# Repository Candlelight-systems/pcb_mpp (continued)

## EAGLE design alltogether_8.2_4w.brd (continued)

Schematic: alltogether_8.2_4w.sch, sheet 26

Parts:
C434: 120n; 0402-CAP
C435, C436, C446, C447: 0.1u; 0402-CAP
C437, C438, C439, C440, C443: 0.1u; 0402
C441, C442: 1n; 0402
C444: 0.1u; 0603-CAP
C445: 22u; 0805
C448: 1n; 0402-CAP
D216, D217, D218, D219, D220, D221, D222: BAT20JFILM; SOD-323
D223, D224: TVSSMA; SMA-DIODE
IC65: OPA237U; SO08
IC66, IC67: INA118U; SO08
JP63, JP64, JP65: JUMPER-PAD-3-NC_BY_PASTE; PAD-JUMPER-3-NC_BY_PASTE_YES_SILK_FULL_BOX
K27: DSBT2-M-2D-DC1.5V; DS-BT
LED21: GREEN; CHIPLED_0603
Q38: MOSFET-NCHANNELAO3404A; SOT23-3
R512, R518, R522, R526, R528: 10k; 0402-RES
R513: 0.001; 2512
R514: 0; 0402-RES
R515: 125; 1206
R516, R519, R530, R531: 250; 0402-RES
R517, R529: 100k; 0402-RES
R520, R521: 47; 0402-RES
R523: 0; 1206
R524, R525: 125; 0402-RES
R527: 0; 0805
TP87, TP88, TP89, TP90: TESTPOINT0.1"; 1X01_ROUND
U$95, U$96, U$97: SPTAF1/2-3.5
U$98: MUX509; R-PDSO-G16

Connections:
A0: TP90.1, U$98.P$1 (A0); also elsewhere on the board
DAC11: R516.1, R529.2, TP89.1; also elsewhere on the board
FB11: JP65.3, R528.1
GND: C434.2, C435.2, C436.2, C437.2, C438.2, C439.1, C440.1, C441.1, C442.2, C446.1, C447.1, D223.C, D224.C, IC66.5 (REF), IC67.5 (REF), Q38.2 (S), R517.1, R522.1, R529.1, U$96.P$1, U$96.P$2, U$98.P$6 (S3A), U$98.P$11 (S3B), U$98.P$15 (GND); also elsewhere on the board
unnamed: D216.A, D217.C, K27.4, R513.2, R526.1, R531.1
unnamed: K27.13, R519.2
unnamed: IC66.1 (RG), R515.1
unnamed: IC66.8 (RG), R515.2
unnamed: C434.1, IC65.3 (+IN), R516.2
unnamed: D218.A, K27.16 (-), Q38.3 (D), R518.1
unnamed: LED21.C, R518.2
unnamed: C443.1, C444.1, IC65.2 (-IN), JP65.2, R522.2
unnamed: C443.2, C445.2, R512.2, R513.1, R527.2, R530.1, U$95.P$3, U$95.P$4
unnamed: IC66.6 (OUT), R520.1
unnamed: IC67.6 (OUT), JP63.3, R521.1, R528.2
unnamed: C444.2, C445.1, IC65.6 (OUT), R514.1, R527.1
unnamed: IC67.1 (RG), R523.1
unnamed: IC67.8 (RG), R523.2
unnamed: IC67.2 (-IN), JP63.2
unnamed: IC67.3 (+IN), JP64.2
unnamed: D221.C, D222.A, D224.A, JP63.1, R524.2
unnamed: R524.1, U$97.P$3, U$97.P$4
unnamed: D219.C, D220.A, D223.A, JP64.1, R525.2
unnamed: R525.1, U$97.P$1, U$97.P$2
unnamed: JP64.3, R526.2
unnamed: JP65.1, R512.1, R519.1
unnamed: R514.2, U$95.P$1, U$95.P$2
unnamed: IC66.2 (-IN), U$98.P$8 (DA)
unnamed: IC66.3 (+IN), U$98.P$9 (DB)
unnamed: C448.2, R531.2, U$98.P$10 (S4B)
unnamed: C448.1, R530.2, U$98.P$7 (S4A)
OUT11: K27.8 (S), K27.9 (S), U$96.P$3, U$96.P$4
SENSEI11: C442.1, R520.2, TP87.1; also elsewhere on the board
SENSEV11: C441.2, R521.2, TP88.1; also elsewhere on the board
SWITCH11: Q38.1 (G), R517.2; also elsewhere on the board
VCC: C436.1, C438.1, C440.2, C446.2, D216.C, D218.C, D220.C, D222.C, IC65.7 (V+), IC66.7 (V+), IC67.7 (V+), K27.1 (+), LED21.A, U$98.P$2 (EN), U$98.P$14 (V+), U$98.P$16 (A1); also elsewhere on the board
VDD: C435.1, C437.1, C439.2, C447.2, D217.A, D219.A, D221.A, IC65.4 (V-), IC66.4 (V-), IC67.4 (V-), U$98.P$3 (V-); also elsewhere on the board

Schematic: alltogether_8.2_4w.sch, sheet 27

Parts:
C464: 120n; 0402-CAP
C465, C466, C476, C477: 0.1u; 0402-CAP
C467, C468, C469, C470, C473: 0.1u; 0402
C471, C472: 1n; 0402
C474: 0.1u; 0603-CAP
C475: 22u; 0805
C478: 1n; 0402-CAP
D234, D235, D236, D237, D238, D239, D240: BAT20JFILM; SOD-323
D241, D242: TVSSMA; SMA-DIODE
IC71: OPA237U; SO08
IC72, IC73: INA118U; SO08
JP69, JP70, JP71: JUMPER-PAD-3-NC_BY_PASTE; PAD-JUMPER-3-NC_BY_PASTE_YES_SILK_FULL_BOX
K29: DSBT2-M-2D-DC1.5V; DS-BT
LED23: GREEN; CHIPLED_0603
Q40: MOSFET-NCHANNELAO3404A; SOT23-3
R552, R558, R562, R566, R568: 10k; 0402-RES
R553: 0.001; 2512
R554: 0; 0402-RES
R555: 125; 1206
R556, R559, R570, R571: 250; 0402-RES
R557, R569: 100k; 0402-RES
R560, R561: 47; 0402-RES
R563: 0; 1206
R564, R565: 125; 0402-RES
R567: 0; 0805
TP95, TP96, TP97, TP98: TESTPOINT0.1"; 1X01_ROUND
U$103, U$104, U$105: SPTAF1/2-3.5
U$106: MUX509; R-PDSO-G16

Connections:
A0: TP98.1, U$106.P$1 (A0); also elsewhere on the board
DAC12: R556.1, R569.2, TP97.1; also elsewhere on the board
FB12: JP71.3, R568.1
GND: C464.2, C465.2, C466.2, C467.2, C468.2, C469.1, C470.1, C471.1, C472.2, C476.1, C477.1, D241.C, D242.C, IC72.5 (REF), IC73.5 (REF), Q40.2 (S), R557.1, R562.1, R569.1, U$104.P$1, U$104.P$2, U$106.P$6 (S3A), U$106.P$11 (S3B), U$106.P$15 (GND); also elsewhere on the board
unnamed: D234.A, D235.C, K29.4, R553.2, R566.1, R571.1
unnamed: K29.13, R559.2
unnamed: IC72.1 (RG), R555.1
unnamed: IC72.8 (RG), R555.2
unnamed: C464.1, IC71.3 (+IN), R556.2
unnamed: D236.A, K29.16 (-), Q40.3 (D), R558.1
unnamed: LED23.C, R558.2
unnamed: C473.1, C474.1, IC71.2 (-IN), JP71.2, R562.2
unnamed: C473.2, C475.2, R552.2, R553.1, R567.2, R570.1, U$103.P$3, U$103.P$4
unnamed: IC72.6 (OUT), R560.1
unnamed: IC73.6 (OUT), JP69.3, R561.1, R568.2
unnamed: C474.2, C475.1, IC71.6 (OUT), R554.1, R567.1
unnamed: IC73.1 (RG), R563.1
unnamed: IC73.8 (RG), R563.2
unnamed: IC73.2 (-IN), JP69.2
unnamed: IC73.3 (+IN), JP70.2
unnamed: D239.C, D240.A, D242.A, JP69.1, R564.2
unnamed: R564.1, U$105.P$3, U$105.P$4
unnamed: D237.C, D238.A, D241.A, JP70.1, R565.2
unnamed: R565.1, U$105.P$1, U$105.P$2
unnamed: JP70.3, R566.2
unnamed: JP71.1, R552.1, R559.1
unnamed: R554.2, U$103.P$1, U$103.P$2
unnamed: IC72.2 (-IN), U$106.P$8 (DA)
unnamed: IC72.3 (+IN), U$106.P$9 (DB)
unnamed: C478.2, R571.2, U$106.P$10 (S4B)
unnamed: C478.1, R570.2, U$106.P$7 (S4A)
OUT12: K29.8 (S), K29.9 (S), U$104.P$3, U$104.P$4
SENSEI12: C472.1, R560.2, TP95.1; also elsewhere on the board
SENSEV12: C471.2, R561.2, TP96.1; also elsewhere on the board
SWITCH12: Q40.1 (G), R557.2; also elsewhere on the board
VCC: C466.1, C468.1, C470.2, C476.2, D234.C, D236.C, D238.C, D240.C, IC71.7 (V+), IC72.7 (V+), IC73.7 (V+), K29.1 (+), LED23.A, U$106.P$2 (EN), U$106.P$14 (V+), U$106.P$16 (A1); also elsewhere on the board
VDD: C465.1, C467.1, C469.2, C477.2, D235.A, D237.A, D239.A, IC71.4 (V-), IC72.4 (V-), IC73.4 (V-), U$106.P$3 (V-); also elsewhere on the board

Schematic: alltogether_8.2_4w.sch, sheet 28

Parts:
C494: 120n; 0402-CAP
C495, C496, C506, C507: 0.1u; 0402-CAP
C497, C498, C499, C500, C503: 0.1u; 0402
C501, C502: 1n; 0402
C504: 0.1u; 0603-CAP
C505: 22u; 0805
C508: 1n; 0402-CAP
D252, D253, D254, D255, D256, D257, D258: BAT20JFILM; SOD-323
D259, D260: TVSSMA; SMA-DIODE
IC77: OPA237U; SO08
IC78, IC79: INA118U; SO08
JP75, JP76, JP77: JUMPER-PAD-3-NC_BY_PASTE; PAD-JUMPER-3-NC_BY_PASTE_YES_SILK_FULL_BOX
K31: DSBT2-M-2D-DC1.5V; DS-BT
LED25: GREEN; CHIPLED_0603
Q42: MOSFET-NCHANNELAO3404A; SOT23-3
R592, R598, R602, R606, R608: 10k; 0402-RES
R593: 0.001; 2512
R594: 0; 0402-RES
R595: 125; 1206
R596, R599, R610, R611: 250; 0402-RES
R597, R609: 100k; 0402-RES
R600, R601: 47; 0402-RES
R603: 0; 1206
R604, R605: 125; 0402-RES
R607: 0; 0805
TP103, TP104, TP105, TP106: TESTPOINT0.1"; 1X01_ROUND
U$111, U$112, U$113: SPTAF1/2-3.5
U$114: MUX509; R-PDSO-G16

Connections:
A0: TP106.1, U$114.P$1 (A0); also elsewhere on the board
DAC13: R596.1, R609.2, TP105.1; also elsewhere on the board
FB13: JP77.3, R608.1
GND: C494.2, C495.2, C496.2, C497.2, C498.2, C499.1, C500.1, C501.1, C502.2, C506.1, C507.1, D259.C, D260.C, IC78.5 (REF), IC79.5 (REF), Q42.2 (S), R597.1, R602.1, R609.1, U$112.P$1, U$112.P$2, U$114.P$6 (S3A), U$114.P$11 (S3B), U$114.P$15 (GND); also elsewhere on the board
unnamed: D252.A, D253.C, K31.4, R593.2, R606.1, R611.1
unnamed: K31.13, R599.2
unnamed: IC78.1 (RG), R595.1
unnamed: IC78.8 (RG), R595.2
unnamed: C494.1, IC77.3 (+IN), R596.2
unnamed: D254.A, K31.16 (-), Q42.3 (D), R598.1
unnamed: LED25.C, R598.2
unnamed: C503.1, C504.1, IC77.2 (-IN), JP77.2, R602.2
unnamed: C503.2, C505.2, R592.2, R593.1, R607.2, R610.1, U$111.P$3, U$111.P$4
unnamed: IC78.6 (OUT), R600.1
unnamed: IC79.6 (OUT), JP75.3, R601.1, R608.2
unnamed: C504.2, C505.1, IC77.6 (OUT), R594.1, R607.1
unnamed: IC79.1 (RG), R603.1
unnamed: IC79.8 (RG), R603.2
unnamed: IC79.2 (-IN), JP75.2
unnamed: IC79.3 (+IN), JP76.2
unnamed: D257.C, D258.A, D260.A, JP75.1, R604.2
unnamed: R604.1, U$113.P$3, U$113.P$4
unnamed: D255.C, D256.A, D259.A, JP76.1, R605.2
unnamed: R605.1, U$113.P$1, U$113.P$2
unnamed: JP76.3, R606.2
unnamed: JP77.1, R592.1, R599.1
unnamed: R594.2, U$111.P$1, U$111.P$2
unnamed: IC78.2 (-IN), U$114.P$8 (DA)
unnamed: IC78.3 (+IN), U$114.P$9 (DB)
unnamed: C508.2, R611.2, U$114.P$10 (S4B)
unnamed: C508.1, R610.2, U$114.P$7 (S4A)
OUT13: K31.8 (S), K31.9 (S), U$112.P$3, U$112.P$4
SENSEI13: C502.1, R600.2, TP103.1; also elsewhere on the board
SENSEV13: C501.2, R601.2, TP104.1; also elsewhere on the board
SWITCH13: Q42.1 (G), R597.2; also elsewhere on the board
VCC: C496.1, C498.1, C500.2, C506.2, D252.C, D254.C, D256.C, D258.C, IC77.7 (V+), IC78.7 (V+), IC79.7 (V+), K31.1 (+), LED25.A, U$114.P$2 (EN), U$114.P$14 (V+), U$114.P$16 (A1); also elsewhere on the board
VDD: C495.1, C497.1, C499.2, C507.2, D253.A, D255.A, D257.A, IC77.4 (V-), IC78.4 (V-), IC79.4 (V-), U$114.P$3 (V-); also elsewhere on the board

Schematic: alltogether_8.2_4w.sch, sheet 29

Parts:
C524: 120n; 0402-CAP
C525, C526, C536, C537: 0.1u; 0402-CAP
C527, C528, C529, C530, C533: 0.1u; 0402
C531, C532: 1n; 0402
C534: 0.1u; 0603-CAP
C535: 22u; 0805
C538: 1n; 0402-CAP
D270, D271, D272, D273, D274, D275, D276: BAT20JFILM; SOD-323
D277, D278: TVSSMA; SMA-DIODE
IC83: OPA237U; SO08
IC84, IC85: INA118U; SO08
JP81, JP82, JP83: JUMPER-PAD-3-NC_BY_PASTE; PAD-JUMPER-3-NC_BY_PASTE_YES_SILK_FULL_BOX
K33: DSBT2-M-2D-DC1.5V; DS-BT
LED27: GREEN; CHIPLED_0603
Q44: MOSFET-NCHANNELAO3404A; SOT23-3
R632, R638, R642, R646, R648: 10k; 0402-RES
R633: 0.001; 2512
R634: 0; 0402-RES
R635: 125; 1206
R636, R639, R650, R651: 250; 0402-RES
R637, R649: 100k; 0402-RES
R640, R641: 47; 0402-RES
R643: 0; 1206
R644, R645: 125; 0402-RES
R647: 0; 0805
TP111, TP112, TP113, TP114: TESTPOINT0.1"; 1X01_ROUND
U$119, U$120, U$121: SPTAF1/2-3.5
U$122: MUX509; R-PDSO-G16

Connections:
A0: TP114.1, U$122.P$1 (A0); also elsewhere on the board
DAC14: R636.1, R649.2, TP113.1; also elsewhere on the board
FB14: JP83.3, R648.1
GND: C524.2, C525.2, C526.2, C527.2, C528.2, C529.1, C530.1, C531.1, C532.2, C536.1, C537.1, D277.C, D278.C, IC84.5 (REF), IC85.5 (REF), Q44.2 (S), R637.1, R642.1, R649.1, U$120.P$1, U$120.P$2, U$122.P$6 (S3A), U$122.P$11 (S3B), U$122.P$15 (GND); also elsewhere on the board
unnamed: D270.A, D271.C, K33.4, R633.2, R646.1, R651.1
unnamed: K33.13, R639.2
unnamed: IC84.1 (RG), R635.1
unnamed: IC84.8 (RG), R635.2
unnamed: C524.1, IC83.3 (+IN), R636.2
unnamed: D272.A, K33.16 (-), Q44.3 (D), R638.1
unnamed: LED27.C, R638.2
unnamed: C533.1, C534.1, IC83.2 (-IN), JP83.2, R642.2
unnamed: C533.2, C535.2, R632.2, R633.1, R647.2, R650.1, U$119.P$3, U$119.P$4
unnamed: IC84.6 (OUT), R640.1
unnamed: IC85.6 (OUT), JP81.3, R641.1, R648.2
unnamed: C534.2, C535.1, IC83.6 (OUT), R634.1, R647.1
unnamed: IC85.1 (RG), R643.1
unnamed: IC85.8 (RG), R643.2
unnamed: IC85.2 (-IN), JP81.2
unnamed: IC85.3 (+IN), JP82.2
unnamed: D275.C, D276.A, D278.A, JP81.1, R644.2
unnamed: R644.1, U$121.P$3, U$121.P$4
unnamed: D273.C, D274.A, D277.A, JP82.1, R645.2
unnamed: R645.1, U$121.P$1, U$121.P$2
unnamed: JP82.3, R646.2
unnamed: JP83.1, R632.1, R639.1
unnamed: R634.2, U$119.P$1, U$119.P$2
unnamed: IC84.2 (-IN), U$122.P$8 (DA)
unnamed: IC84.3 (+IN), U$122.P$9 (DB)
unnamed: C538.2, R651.2, U$122.P$10 (S4B)
unnamed: C538.1, R650.2, U$122.P$7 (S4A)
OUT14: K33.8 (S), K33.9 (S), U$120.P$3, U$120.P$4
SENSEI14: C532.1, R640.2, TP111.1; also elsewhere on the board
SENSEV14: C531.2, R641.2, TP112.1; also elsewhere on the board
SWITCH14: Q44.1 (G), R637.2; also elsewhere on the board
VCC: C526.1, C528.1, C530.2, C536.2, D270.C, D272.C, D274.C, D276.C, IC83.7 (V+), IC84.7 (V+), IC85.7 (V+), K33.1 (+), LED27.A, U$122.P$2 (EN), U$122.P$14 (V+), U$122.P$16 (A1); also elsewhere on the board
VDD: C525.1, C527.1, C529.2, C537.2, D271.A, D273.A, D275.A, IC83.4 (V-), IC84.4 (V-), IC85.4 (V-), U$122.P$3 (V-); also elsewhere on the board

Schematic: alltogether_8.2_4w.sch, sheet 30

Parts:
C554: 120n; 0402-CAP
C555, C556, C566, C567: 0.1u; 0402-CAP
C557, C558, C559, C560, C563: 0.1u; 0402
C561, C562: 1n; 0402
C564: 0.1u; 0603-CAP
C565: 22u; 0805
C568: 1n; 0402-CAP
D288, D289, D290, D291, D292, D293, D294: BAT20JFILM; SOD-323
D295, D296: TVSSMA; SMA-DIODE
IC89: OPA237U; SO08
IC90, IC91: INA118U; SO08
JP87, JP88, JP89: JUMPER-PAD-3-NC_BY_PASTE; PAD-JUMPER-3-NC_BY_PASTE_YES_SILK_FULL_BOX
K35: DSBT2-M-2D-DC1.5V; DS-BT
LED29: GREEN; CHIPLED_0603
Q46: MOSFET-NCHANNELAO3404A; SOT23-3
R672, R678, R682, R686, R688: 10k; 0402-RES
R673: 0.001; 2512
R674: 0; 0402-RES
R675: 125; 1206
R676, R679, R690, R691: 250; 0402-RES
R677, R689: 100k; 0402-RES
R680, R681: 47; 0402-RES
R683: 0; 1206
R684, R685: 125; 0402-RES
R687: 0; 0805
TP119, TP120, TP121, TP122: TESTPOINT0.1"; 1X01_ROUND
U$127, U$128, U$129: SPTAF1/2-3.5
U$130: MUX509; R-PDSO-G16

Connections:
A0: TP122.1, U$130.P$1 (A0); also elsewhere on the board
DAC15: R676.1, R689.2, TP121.1; also elsewhere on the board
FB15: JP89.3, R688.1
GND: C554.2, C555.2, C556.2, C557.2, C558.2, C559.1, C560.1, C561.1, C562.2, C566.1, C567.1, D295.C, D296.C, IC90.5 (REF), IC91.5 (REF), Q46.2 (S), R677.1, R682.1, R689.1, U$128.P$1, U$128.P$2, U$130.P$6 (S3A), U$130.P$11 (S3B), U$130.P$15 (GND); also elsewhere on the board
unnamed: D288.A, D289.C, K35.4, R673.2, R686.1, R691.1
unnamed: K35.13, R679.2
unnamed: IC90.1 (RG), R675.1
unnamed: IC90.8 (RG), R675.2
unnamed: C554.1, IC89.3 (+IN), R676.2
unnamed: D290.A, K35.16 (-), Q46.3 (D), R678.1
unnamed: LED29.C, R678.2
unnamed: C563.1, C564.1, IC89.2 (-IN), JP89.2, R682.2
unnamed: C563.2, C565.2, R672.2, R673.1, R687.2, R690.1, U$127.P$3, U$127.P$4
unnamed: IC90.6 (OUT), R680.1
unnamed: IC91.6 (OUT), JP87.3, R681.1, R688.2
unnamed: C564.2, C565.1, IC89.6 (OUT), R674.1, R687.1
unnamed: IC91.1 (RG), R683.1
unnamed: IC91.8 (RG), R683.2
unnamed: IC91.2 (-IN), JP87.2
unnamed: IC91.3 (+IN), JP88.2
unnamed: D293.C, D294.A, D296.A, JP87.1, R684.2
unnamed: R684.1, U$129.P$3, U$129.P$4
unnamed: D291.C, D292.A, D295.A, JP88.1, R685.2
unnamed: R685.1, U$129.P$1, U$129.P$2
unnamed: JP88.3, R686.2
unnamed: JP89.1, R672.1, R679.1
unnamed: R674.2, U$127.P$1, U$127.P$2
unnamed: IC90.2 (-IN), U$130.P$8 (DA)
unnamed: IC90.3 (+IN), U$130.P$9 (DB)
unnamed: C568.2, R691.2, U$130.P$10 (S4B)
unnamed: C568.1, R690.2, U$130.P$7 (S4A)
OUT15: K35.8 (S), K35.9 (S), U$128.P$3, U$128.P$4
SENSEI15: C562.1, R680.2, TP119.1; also elsewhere on the board
SENSEV15: C561.2, R681.2, TP120.1; also elsewhere on the board
SWITCH15: Q46.1 (G), R677.2; also elsewhere on the board
VCC: C556.1, C558.1, C560.2, C566.2, D288.C, D290.C, D292.C, D294.C, IC89.7 (V+), IC90.7 (V+), IC91.7 (V+), K35.1 (+), LED29.A, U$130.P$2 (EN), U$130.P$14 (V+), U$130.P$16 (A1); also elsewhere on the board
VDD: C555.1, C557.1, C559.2, C567.2, D289.A, D291.A, D293.A, IC89.4 (V-), IC90.4 (V-), IC91.4 (V-), U$130.P$3 (V-); also elsewhere on the board

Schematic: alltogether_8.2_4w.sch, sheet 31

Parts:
C584: 120n; 0402-CAP
C585, C586, C596, C597: 0.1u; 0402-CAP
C587, C588, C589, C590, C593: 0.1u; 0402
C591, C592: 1n; 0402
C594: 0.1u; 0603-CAP
C595: 22u; 0805
C598: 1n; 0402-CAP
D306, D307, D308, D309, D310, D311, D312: BAT20JFILM; SOD-323
D313, D314: TVSSMA; SMA-DIODE
IC95: OPA237U; SO08
IC96, IC97: INA118U; SO08
JP93, JP94, JP95: JUMPER-PAD-3-NC_BY_PASTE; PAD-JUMPER-3-NC_BY_PASTE_YES_SILK_FULL_BOX
K37: DSBT2-M-2D-DC1.5V; DS-BT
LED31: GREEN; CHIPLED_0603
Q48: MOSFET-NCHANNELAO3404A; SOT23-3
R712, R718, R722, R726, R728: 10k; 0402-RES
R713: 0.001; 2512
R714: 0; 0402-RES
R715: 125; 1206
R716, R719, R730, R731: 250; 0402-RES
R717, R729: 100k; 0402-RES
R720, R721: 47; 0402-RES
R723: 0; 1206
R724, R725: 125; 0402-RES
R727: 0; 0805
TP127, TP128, TP129, TP130: TESTPOINT0.1"; 1X01_ROUND
U$135, U$136, U$137: SPTAF1/2-3.5
U$138: MUX509; R-PDSO-G16

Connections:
A0: TP130.1, U$138.P$1 (A0); also elsewhere on the board
DAC16: R716.1, R729.2, TP129.1; also elsewhere on the board
FB16: JP95.3, R728.1
GND: C584.2, C585.2, C586.2, C587.2, C588.2, C589.1, C590.1, C591.1, C592.2, C596.1, C597.1, D313.C, D314.C, IC96.5 (REF), IC97.5 (REF), Q48.2 (S), R717.1, R722.1, R729.1, U$136.P$1, U$136.P$2, U$138.P$6 (S3A), U$138.P$11 (S3B), U$138.P$15 (GND); also elsewhere on the board
unnamed: D306.A, D307.C, K37.4, R713.2, R726.1, R731.1
unnamed: K37.13, R719.2
unnamed: IC96.1 (RG), R715.1
unnamed: IC96.8 (RG), R715.2
unnamed: C584.1, IC95.3 (+IN), R716.2
unnamed: D308.A, K37.16 (-), Q48.3 (D), R718.1
unnamed: LED31.C, R718.2
unnamed: C593.1, C594.1, IC95.2 (-IN), JP95.2, R722.2
unnamed: C593.2, C595.2, R712.2, R713.1, R727.2, R730.1, U$135.P$3, U$135.P$4
unnamed: IC96.6 (OUT), R720.1
unnamed: IC97.6 (OUT), JP93.3, R721.1, R728.2
unnamed: C594.2, C595.1, IC95.6 (OUT), R714.1, R727.1
unnamed: IC97.1 (RG), R723.1
unnamed: IC97.8 (RG), R723.2
unnamed: IC97.2 (-IN), JP93.2
unnamed: IC97.3 (+IN), JP94.2
unnamed: D311.C, D312.A, D314.A, JP93.1, R724.2
unnamed: R724.1, U$137.P$3, U$137.P$4
unnamed: D309.C, D310.A, D313.A, JP94.1, R725.2
unnamed: R725.1, U$137.P$1, U$137.P$2
unnamed: JP94.3, R726.2
unnamed: JP95.1, R712.1, R719.1
unnamed: R714.2, U$135.P$1, U$135.P$2
unnamed: IC96.2 (-IN), U$138.P$8 (DA)
unnamed: IC96.3 (+IN), U$138.P$9 (DB)
unnamed: C598.2, R731.2, U$138.P$10 (S4B)
unnamed: C598.1, R730.2, U$138.P$7 (S4A)
OUT16: K37.8 (S), K37.9 (S), U$136.P$3, U$136.P$4
SENSEI16: C592.1, R720.2, TP127.1; also elsewhere on the board
SENSEV16: C591.2, R721.2, TP128.1; also elsewhere on the board
SWITCH16: Q48.1 (G), R717.2; also elsewhere on the board
VCC: C586.1, C588.1, C590.2, C596.2, D306.C, D308.C, D310.C, D312.C, IC95.7 (V+), IC96.7 (V+), IC97.7 (V+), K37.1 (+), LED31.A, U$138.P$2 (EN), U$138.P$14 (V+), U$138.P$16 (A1); also elsewhere on the board
VDD: C585.1, C587.1, C589.2, C597.2, D307.A, D309.A, D311.A, IC95.4 (V-), IC96.4 (V-), IC97.4 (V-), U$138.P$3 (V-); also elsewhere on the board

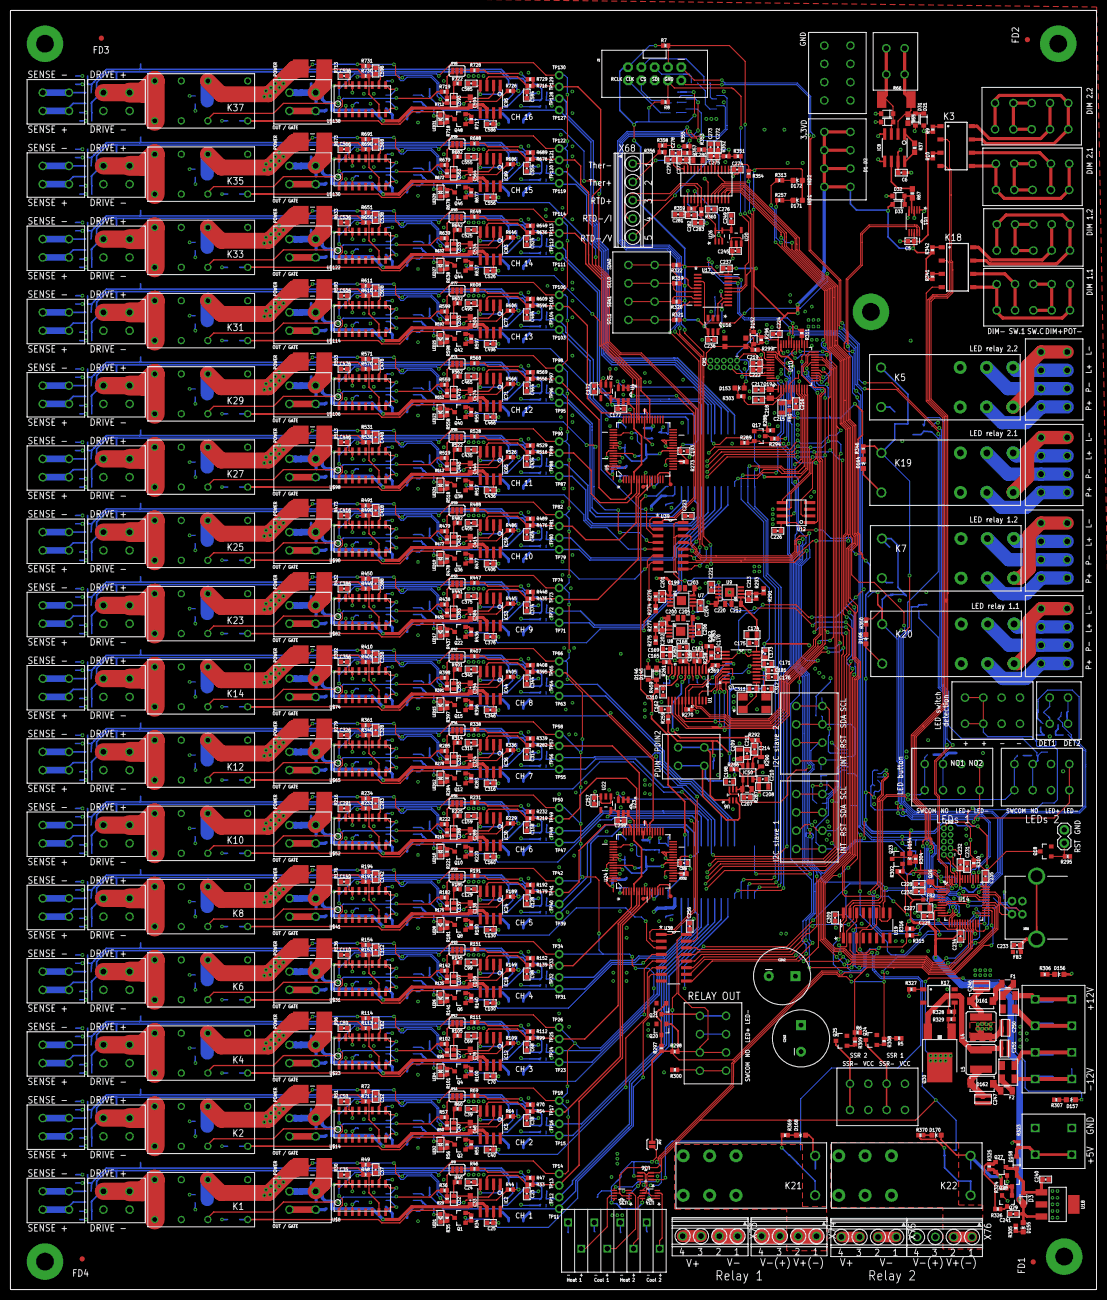
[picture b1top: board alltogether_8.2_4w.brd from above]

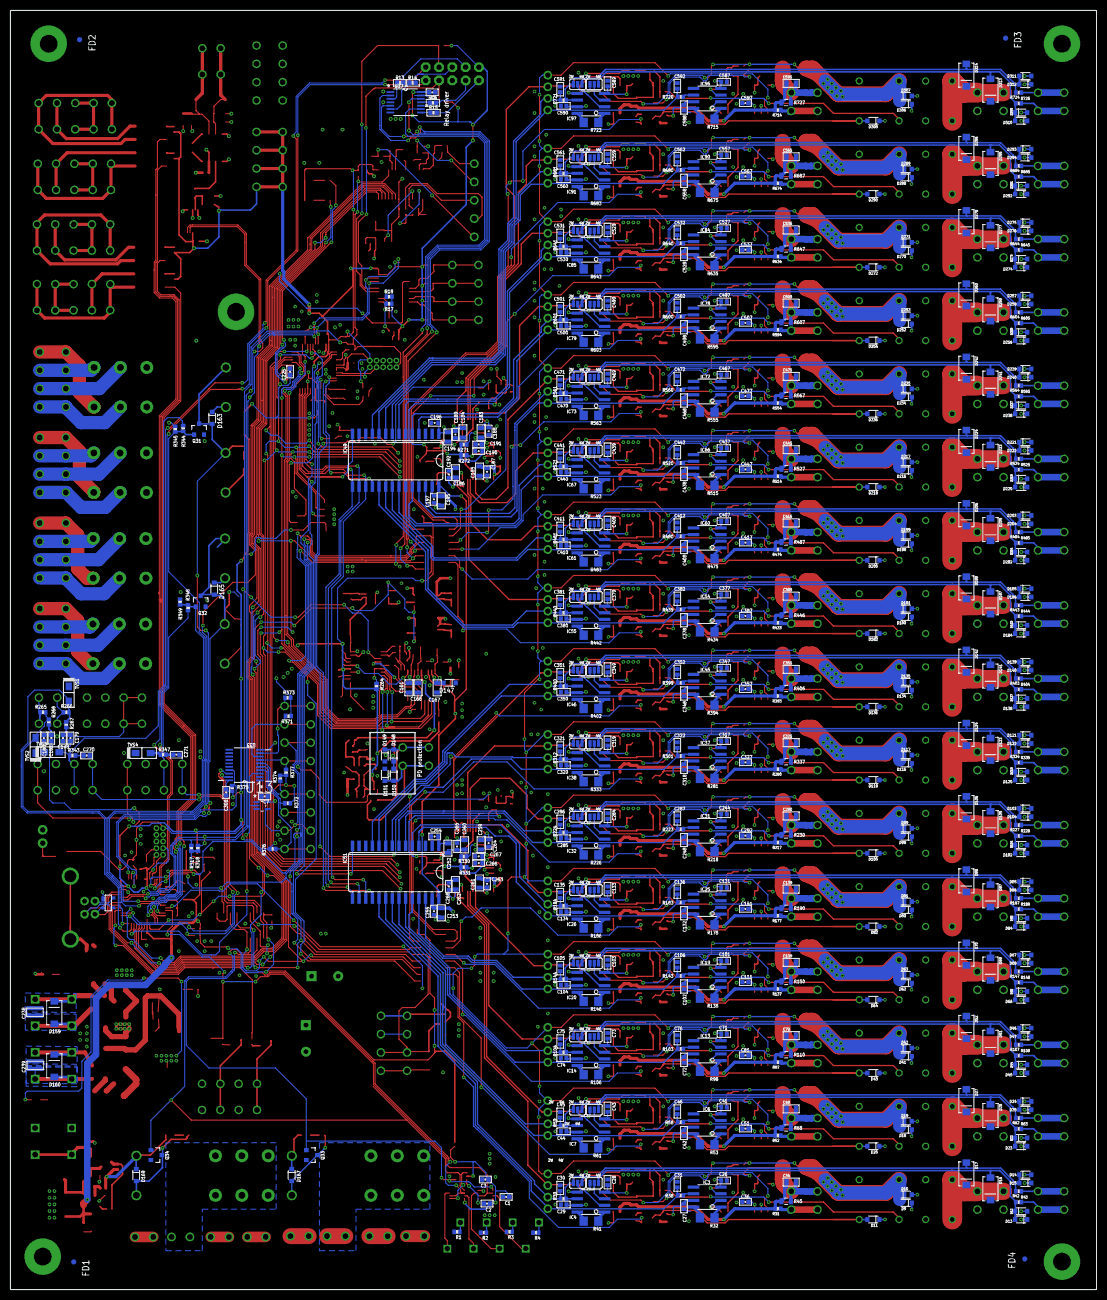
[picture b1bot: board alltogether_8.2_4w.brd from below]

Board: 4 copper layers, 207.6 x 244.5 mm, 1385 parts (573 on the bottom side), 807 nets.

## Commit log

2018-12-05 Add 8.2 board version
